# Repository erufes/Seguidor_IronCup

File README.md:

# Seguidor_IronCup
O objetivo deste projeto é construir e aprimorar um seguidor de linha capaz de ganhar a competição da IronCup 2019. Para isso, o projeto consta de estudo, prototipagem, desing e aprimoramento.  https://www.robocore.net/eventos/ironcup-2019  Edital da competição: https://www.robocore.net/upload/attachments/robocore__regras_seguidor_de_linha_108.pdf

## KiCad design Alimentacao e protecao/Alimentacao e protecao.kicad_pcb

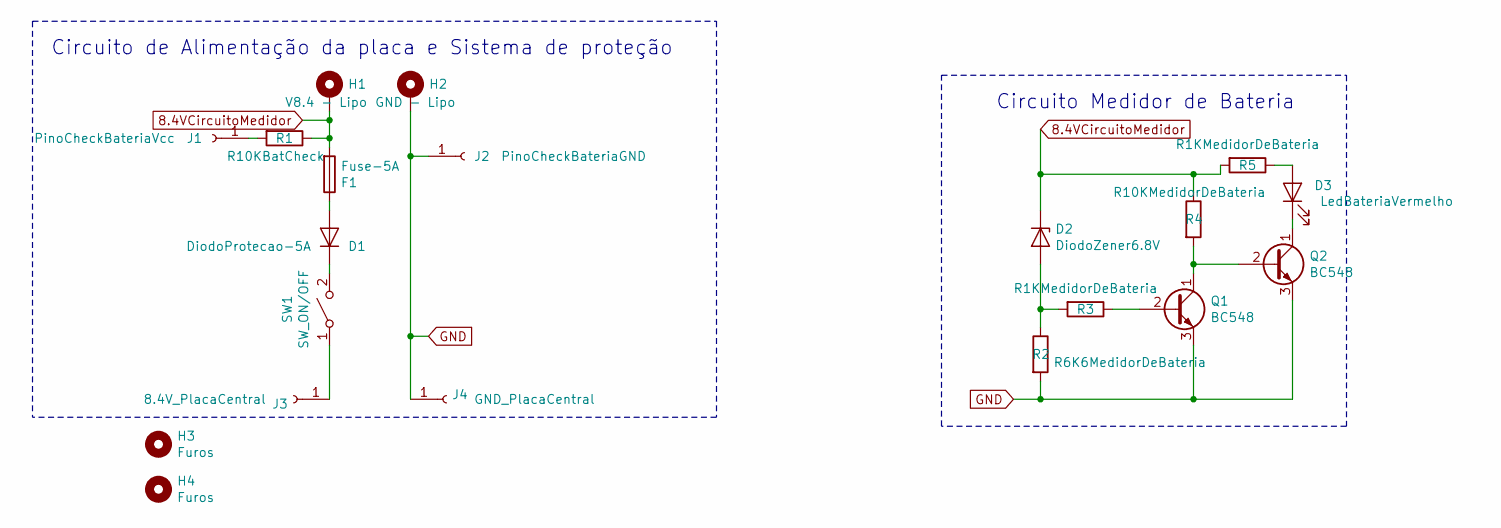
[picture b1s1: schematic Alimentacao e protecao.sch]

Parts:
D1: DiodoProtecao-5A; D_DO-27_P15.24mm_Horizontal
D2: DiodoZener6.8V; D_DO-35_SOD27_P10.16mm_Horizontal
D3: LedBateriaVermelho; LED_D3.0mm
F1: Fuse-5A; Fuseholder_Cylinder-5x20mm_Stelvio-Kontek_PTF78_Horizontal_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
H1: V8.4 - Lipo; SolderWirePad_1x01_Drill1.5mm
H2: GND - Lipo; SolderWirePad_1x01_Drill1.5mm
H3, H4: Furos; SolderWirePad_single_2-5mmDrill
J1: PinoCheckBateriaVcc; PinSocket_1x01_P2.54mm_Vertical
J2: PinoCheckBateriaGND; SolderWirePad_1x01_Drill1.5mm
J3: 8.4V_PlacaCentral; SolderWirePad_1x01_Drill1.2mm
J4: GND_PlacaCentral; SolderWirePad_1x01_Drill1.2mm
Q1, Q2: BC548; TO-92_Wide
R1: R10KBatCheck; R_Axial_DIN0207_L6.3mm_D2.5mm_P10.16mm_Horizontal
R2: R6K6MedidorDeBateria; R_Axial_DIN0207_L6.3mm_D2.5mm_P10.16mm_Horizontal
R3, R5: R1KMedidorDeBateria; R_Axial_DIN0207_L6.3mm_D2.5mm_P10.16mm_Horizontal
R4: R10KMedidorDeBateria; R_Axial_DIN0207_L6.3mm_D2.5mm_P10.16mm_Horizontal
SW1: SW_ON/OFF; Solder_Pad_Custom

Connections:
8.4VCircuitoMedidor: D2.1 (K), F1.2, H1.1, R1.1, R4.1, R5.2
GND: H2.1, J2.1, J4.1, Q1.3 (E), Q2.3 (E), R2.2
unnamed: D1.1 (K), SW1.2 (B)
unnamed: D1.2 (A), F1.1
unnamed: D2.2 (A), R2.1, R3.2
unnamed: D3.1 (K), Q2.1 (C)
unnamed: D3.2 (A), R5.1
unnamed: J1.1, R1.2
unnamed: J3.1, SW1.1 (A)
unnamed: Q1.1 (C), Q2.2 (B), R4.2
unnamed: Q1.2 (B), R3.1

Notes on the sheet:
Circuito de Alimentação da placa e Sistema de proteção
Circuito Medidor de Bateria

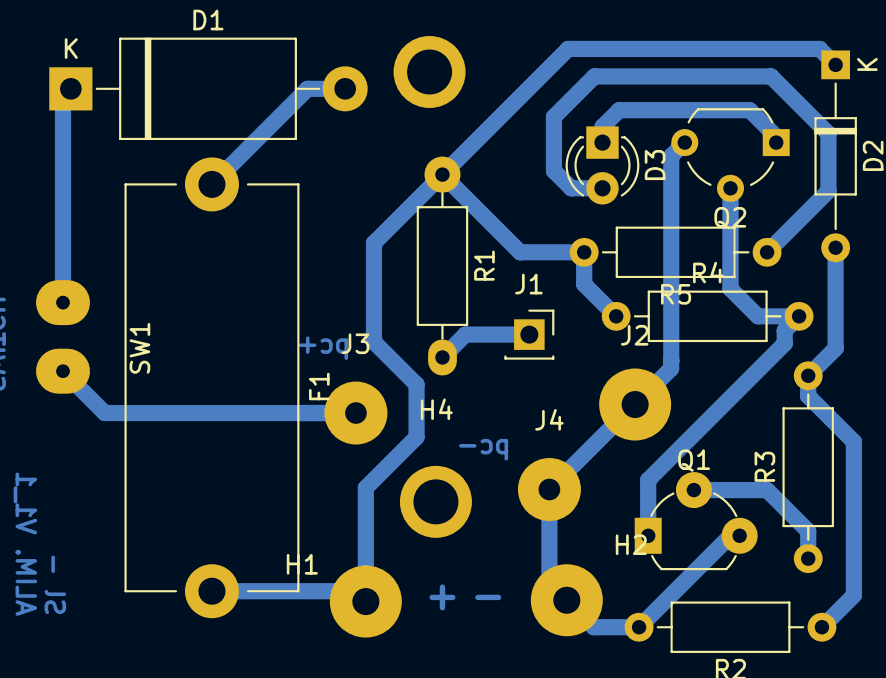
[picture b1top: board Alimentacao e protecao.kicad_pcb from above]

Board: 2 copper layers, 20 parts (0 on the bottom side), 11 nets.

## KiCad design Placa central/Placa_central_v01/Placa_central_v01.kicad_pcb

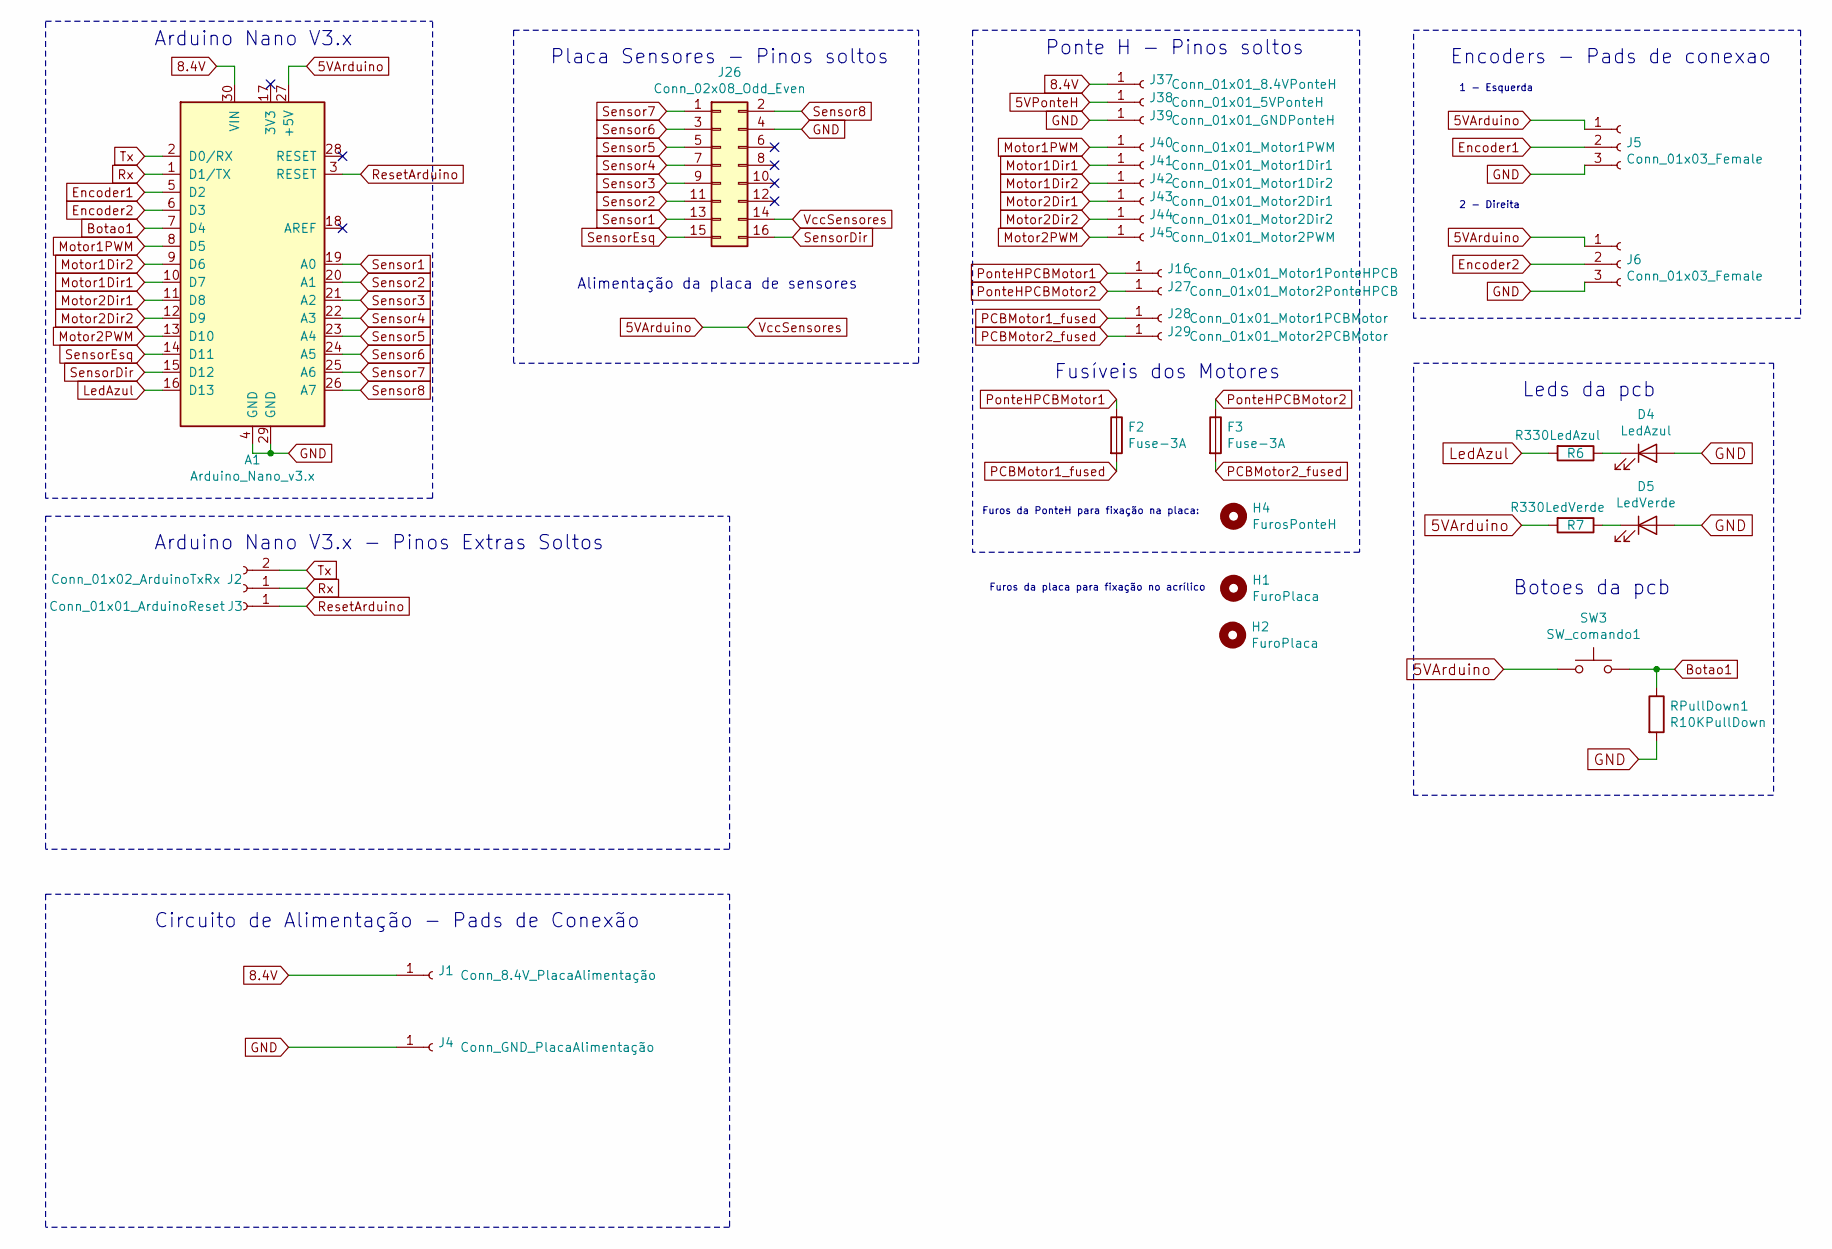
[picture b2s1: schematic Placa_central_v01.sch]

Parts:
A1: Arduino_Nano_v3.x; Arduino_Nano
D4: LedAzul; LED_D3.0mm
D5: LedVerde; LED_D3.0mm
F2, F3: Fuse-3A; Fuseholder_Cylinder-5x20mm_Stelvio-Kontek_PTF78_Horizontal_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
H1, H2: FuroPlaca; SolderWirePad_1x01_Drill2.5mm
H4: FurosPonteH; Ponte_H_furos
J1: Conn_8.4V_PlacaAlimentação; SolderWirePad_1x01_Drill1.2mm
J2: Conn_01x02_ArduinoTxRx; PinSocket_1x02_P2.54mm_Vertical
J3: Conn_01x01_ArduinoReset; PinSocket_1x01_P2.54mm_Vertical
J4: Conn_GND_PlacaAlimentação; SolderWirePad_1x01_Drill1.2mm
J5, J6: Conn_01x03_Female; Molex_KK-254_AE-6410-03A_1x03_P2.54mm_Vertical
J16: Conn_01x01_Motor1PonteHPCB; SolderWirePad_1x01_Drill1.5mm
J26: Conn_02x08_Odd_Even; IDC-Header_2x08_P2.54mm_Horizontal
J27: Conn_01x01_Motor2PonteHPCB; SolderWirePad_1x01_Drill1.5mm
J28: Conn_01x01_Motor1PCBMotor; SolderWirePad_1x01_Drill1.5mm
J29: Conn_01x01_Motor2PCBMotor; SolderWirePad_1x01_Drill1.5mm
J37: Conn_01x01_8.4VPonteH; SolderWirePad_single_1-2mmDrill
J38: Conn_01x01_5VPonteH; SolderWirePad_1x01_Drill1.2mm
J39: Conn_01x01_GNDPonteH; SolderWirePad_1x01_Drill1.2mm
J40: Conn_01x01_Motor1PWM; SolderWirePad_1x01_Drill0.8mm
J41: Conn_01x01_Motor1Dir1; SolderWirePad_1x01_Drill0.8mm
J42: Conn_01x01_Motor1Dir2; SolderWirePad_1x01_Drill0.8mm
J43: Conn_01x01_Motor2Dir1; SolderWirePad_1x01_Drill0.8mm
J44: Conn_01x01_Motor2Dir2; SolderWirePad_1x01_Drill0.8mm
J45: Conn_01x01_Motor2PWM; SolderWirePad_1x01_Drill0.8mm
R6: R330LedAzul; R_Axial_DIN0207_L6.3mm_D2.5mm_P10.16mm_Horizontal
R7: R330LedVerde; R_Axial_DIN0207_L6.3mm_D2.5mm_P10.16mm_Horizontal
RPullDown1: R10KPullDown; R_Axial_DIN0207_L6.3mm_D2.5mm_P10.16mm_Horizontal
SW3: SW_comando1; SW_PUSH_6mm_H5mm

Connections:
5VArduino: A1.27 (+5V), J5.1, J6.1, J26.14, R7.2, SW3.1
5VPonteH: J38.1
8.4V: A1.30 (VIN), J1.1, J37.1
Botao1: A1.7 (D4), RPullDown1.1, SW3.2
Encoder1: A1.5 (D2), J5.2
Encoder2: A1.6 (D3), J6.2
GND: A1.4 (GND), A1.29 (GND), D4.2 (A), D5.2 (A), J4.1, J5.3, J6.3, J26.4, J39.1, RPullDown1.2; also elsewhere on the board
LedAzul: A1.16 (D13), R6.2
Motor1Dir1: A1.10 (D7), J41.1
Motor1Dir2: A1.9 (D6), J42.1
Motor1PWM: A1.8 (D5), J40.1
Motor2Dir1: A1.11 (D8), J43.1
Motor2Dir2: A1.12 (D9), J44.1
Motor2PWM: A1.13 (D10), J45.1
unnamed: D4.1 (K), R6.1
unnamed: D5.1 (K), R7.1
PCBMotor1_fused: F2.2, J28.1
PCBMotor2_fused: F3.2, J29.1
PonteHPCBMotor1: F2.1, J16.1
PonteHPCBMotor2: F3.1, J27.1
ResetArduino: A1.3 (RESET), J3.1
Rx: A1.1 (D1/TX), J2.1
Sensor1: A1.19 (A0), J26.13
Sensor2: A1.20 (A1), J26.11
Sensor3: A1.21 (A2), J26.9
Sensor4: A1.22 (A3), J26.7
Sensor5: A1.23 (A4), J26.5
Sensor6: A1.24 (A5), J26.3
Sensor7: A1.25 (A6), J26.1
Sensor8: A1.26 (A7), J26.2
SensorDir: A1.15 (D12), J26.16
SensorEsq: A1.14 (D11), J26.15
Tx: A1.2 (D0/RX), J2.2

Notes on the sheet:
Ponte H - Pinos soltos
Arduino Nano V3.x
Leds da pcb
Botoes da pcb
Encoders - Pads de conexao
1 - Esquerda
2 - Direita
Alimentação da placa de sensores
Placa Sensores - Pinos soltos
Arduino Nano V3.x - Pinos Extras Soltos
Fusíveis dos Motores
Furos da PonteH para fixação na placa:
Circuito de Alimentação - Pads de Conexão
Furos da placa para fixação no acrílico

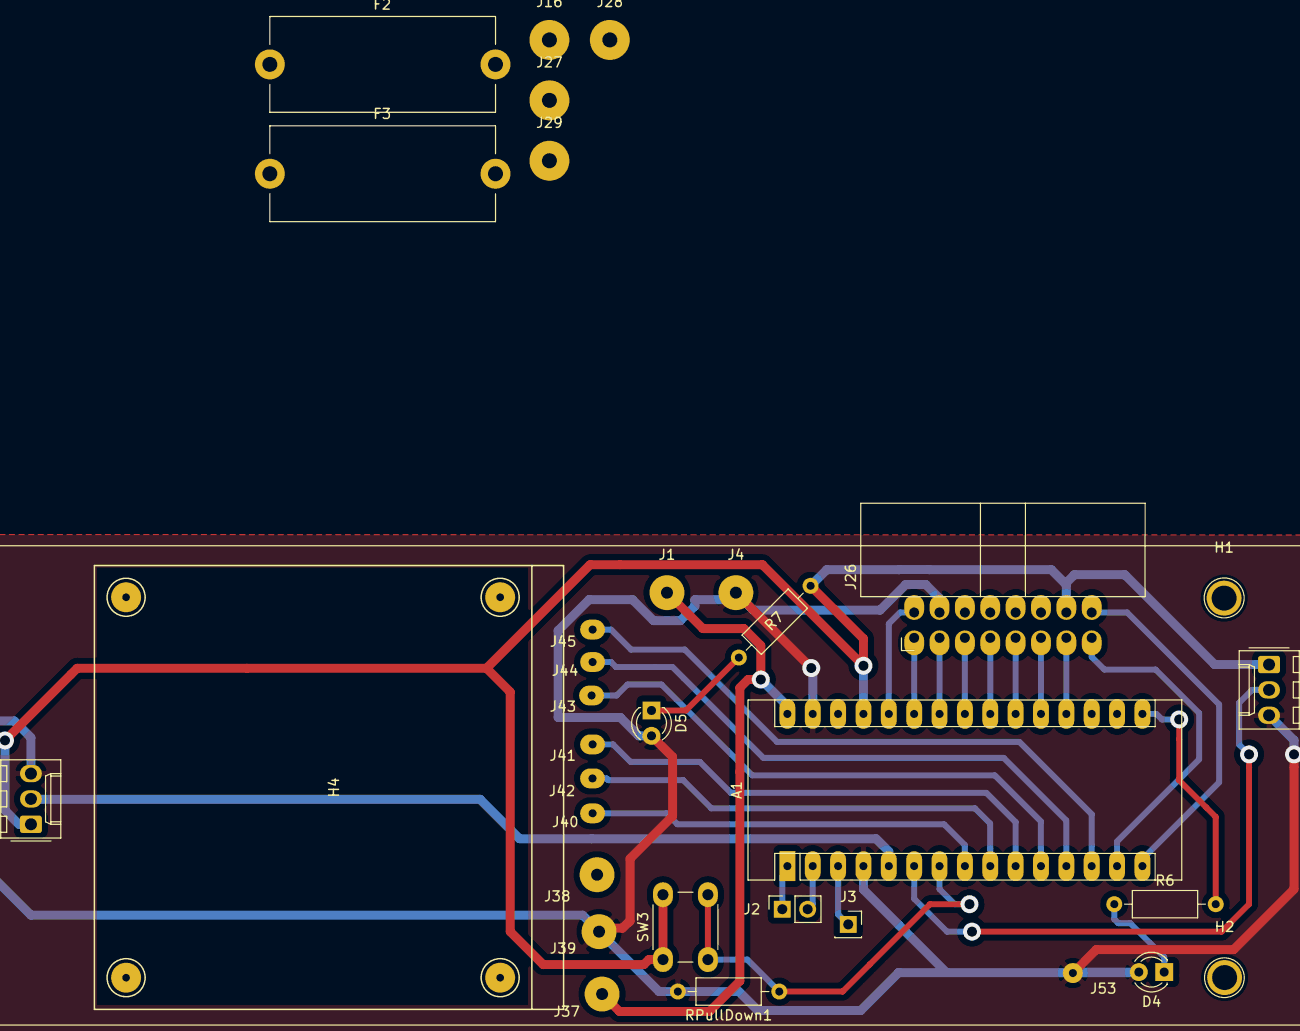
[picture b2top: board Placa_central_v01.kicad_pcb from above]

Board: 2 copper layers, 33 parts (0 on the bottom side), 32 nets.

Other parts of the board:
J53: Conn_01x01_GNDEncoderDir; SolderWirePad_1x01_Drill0.8mm

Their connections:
GND: J53.1; also elsewhere on the board

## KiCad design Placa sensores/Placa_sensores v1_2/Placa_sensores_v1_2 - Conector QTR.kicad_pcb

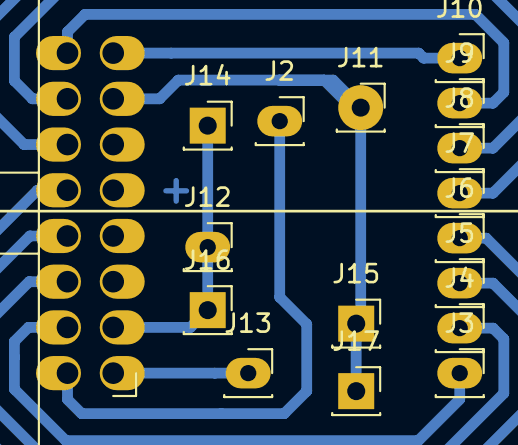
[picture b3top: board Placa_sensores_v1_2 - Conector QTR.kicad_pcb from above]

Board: 2 copper layers, 21 parts (0 on the bottom side), 12 nets.

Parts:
H1, H1#2, H1#3, H2: MountingHole; MountingHole_3mm
J1: Conn_02x08_Odd_Even; IDC-Header_2x08_P2.54mm_Horizontal
J2, J3, J4, J5, J6, J7, J8, J9, J10, J11, J12, J13, J14, J15, J16, J17: Conn_01x01_Female; PinSocket_1x01_P2.54mm_Vertical

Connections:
GND: J1.13, J11.1, J15.1, J17.1
Sensor1: J1.4, J3.1
Sensor2: J1.6, J4.1
Sensor3: J1.8, J5.1
Sensor4: J1.10, J6.1
Sensor5: J1.12, J7.1
Sensor6: J1.14, J8.1
Sensor7: J1.16, J9.1
Sensor8: J1.15, J10.1
SensorDir: J1.1, J13.1
SensorEsq: J1.2, J2.1
VccSensores: J1.3, J12.1, J14.1, J16.1

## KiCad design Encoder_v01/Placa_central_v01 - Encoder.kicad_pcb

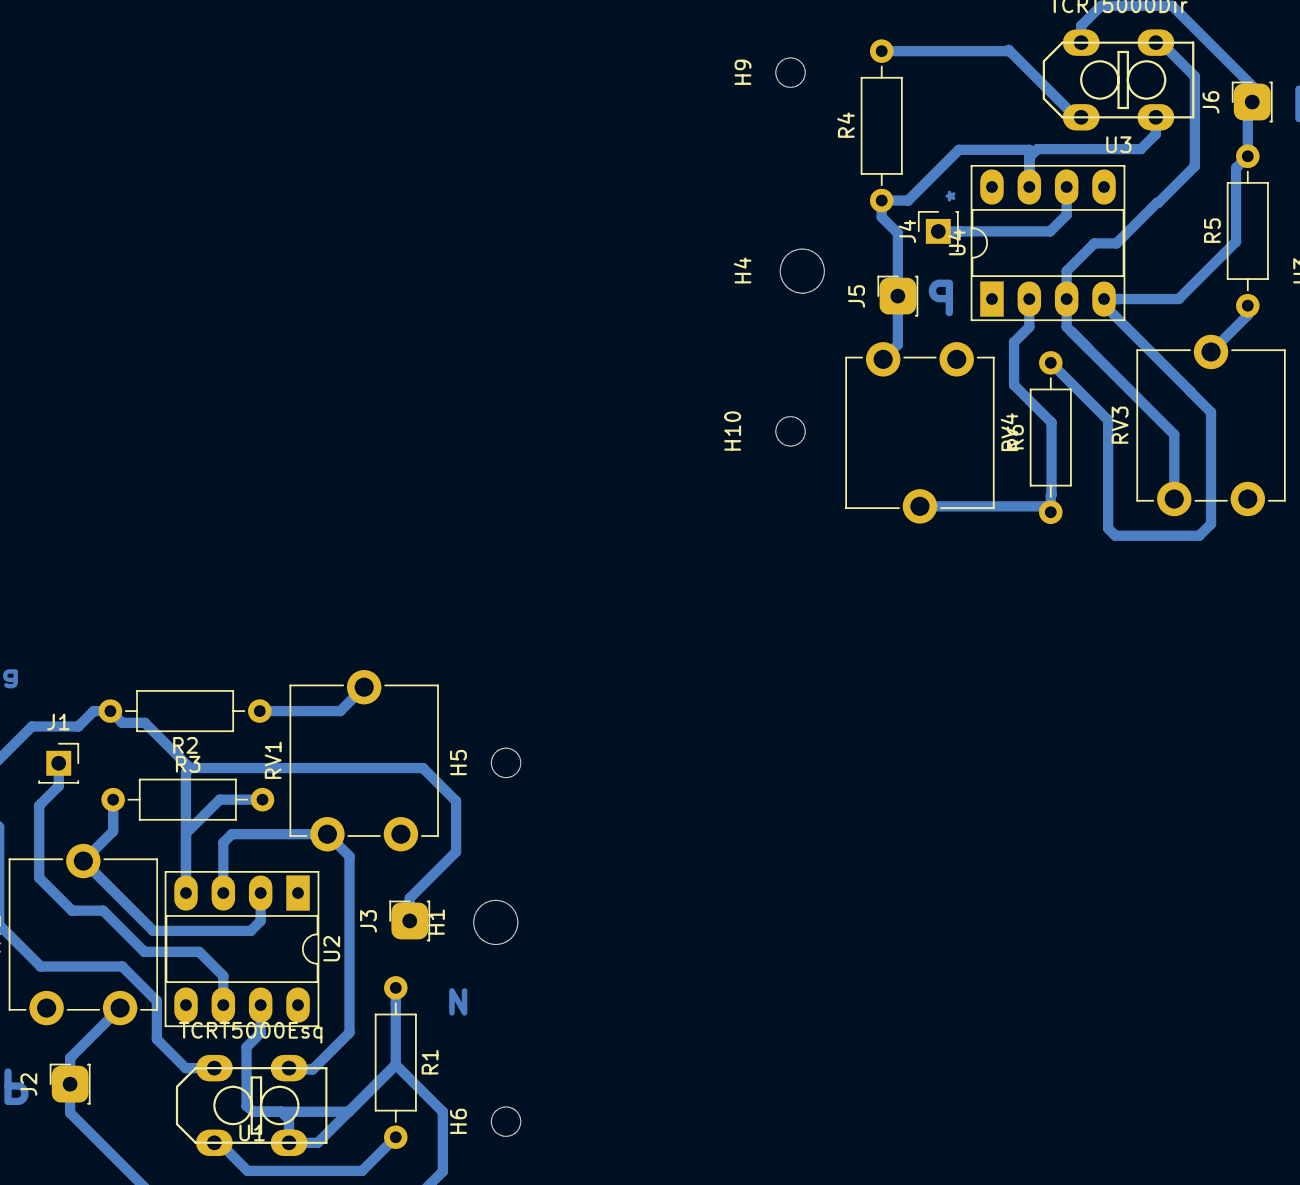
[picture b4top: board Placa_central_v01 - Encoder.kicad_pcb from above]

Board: 2 copper layers, 32 parts (0 on the bottom side), 14 nets.

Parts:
H1: Furo1Esq; MountingHole_3mm
H2: Furo2Esq; MountingHole_3mm
H3: Furo1Dir; MountingHole_3mm
H4: Furo2Dir; MountingHole_3mm
H5: Furo3Esq; MountingHole_2mm
H6: Furo4Esq; MountingHole_2mm
H7: Furo5Esq; MountingHole_2mm
H8: Furo6Esq; MountingHole_2mm
H9: Furo3Dir; MountingHole_2mm
H10: Furo4Dir; MountingHole_2mm
H11: Furo5Dir; MountingHole_2mm
H12: Furo6Dir; MountingHole_2mm
J1, J2, J3, J4, J5, J6: Conn_01x01_Female; PinSocket_1x01_P2.54mm_Vertical
R1: R220ledIREsq; R_Axial_DIN0207_L6.3mm_D2.5mm_P10.16mm_Horizontal
R2: R1KEsq; R_Axial_DIN0207_L6.3mm_D2.5mm_P10.16mm_Horizontal
R3: R10kEsq; R_Axial_DIN0207_L6.3mm_D2.5mm_P10.16mm_Horizontal
R4: R220ledIRDir; R_Axial_DIN0207_L6.3mm_D2.5mm_P10.16mm_Horizontal
R5: R1KDir; R_Axial_DIN0207_L6.3mm_D2.5mm_P10.16mm_Horizontal
R6: R10k; R_Axial_DIN0207_L6.3mm_D2.5mm_P10.16mm_Horizontal
RV1, RV2: R10KPOT_TRIMEsq; Potentiometer_ACP_CA9-V10_Vertical
RV3: R10KPOT_TRIMDir; Potentiometer_ACP_CA9-V10_Vertical
RV4: R10KPOT_TRIM; Potentiometer_ACP_CA9-V10_Vertical
U1: TCRT5000Esq; TCRT5000Extendido
U2: LM741Esq; DIP-8_W7.62mm_Socket_LongPads
U3: TCRT5000Dir; TCRT5000Extendido
U4: LM741; DIP-8_W7.62mm_Socket_LongPads

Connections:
GNDDir: J6.1, R5.2, R6.2, U3.2, U4.4
GNDEsq: J3.1, R2.2, R3.2, U1.2, U2.4
unnamed: R1.2, U1.1
unnamed: R2.1, RV1.2
unnamed: R3.1, RV2.2, U2.2
unnamed: R4.2, U3.1
unnamed: R5.1, RV3.2
unnamed: R6.1, RV4.2, U4.2
unnamed: RV1.3, U1.4, U2.3
unnamed: RV3.3, U3.4, U4.3
SinalEncoderDIr: J4.1, U4.6
SinalEncoderEsq: J1.1, U2.6
VccDir: J5.e1, R4.1, RV4.1, U3.3, U4.7
VccEsq: J2.1, R1.1, RV2.1, U1.3, U2.7

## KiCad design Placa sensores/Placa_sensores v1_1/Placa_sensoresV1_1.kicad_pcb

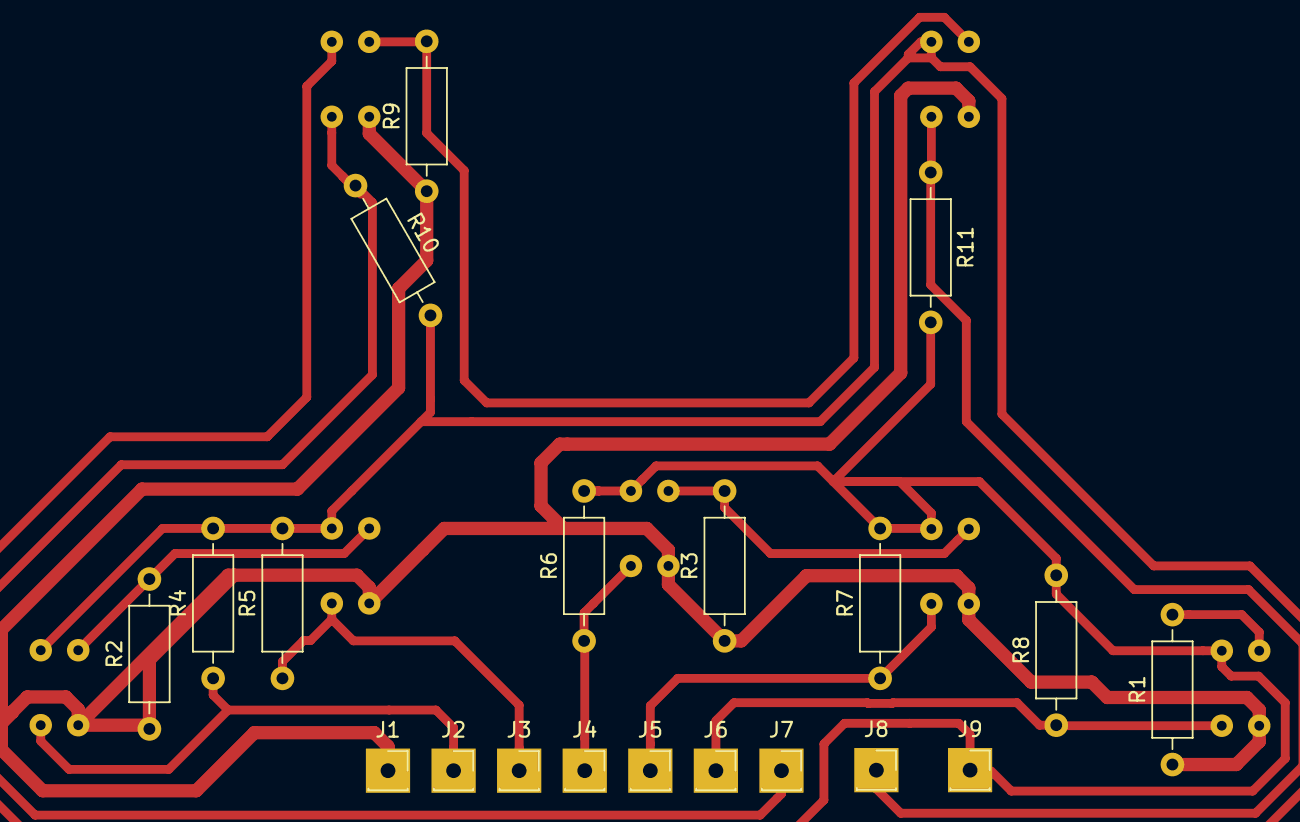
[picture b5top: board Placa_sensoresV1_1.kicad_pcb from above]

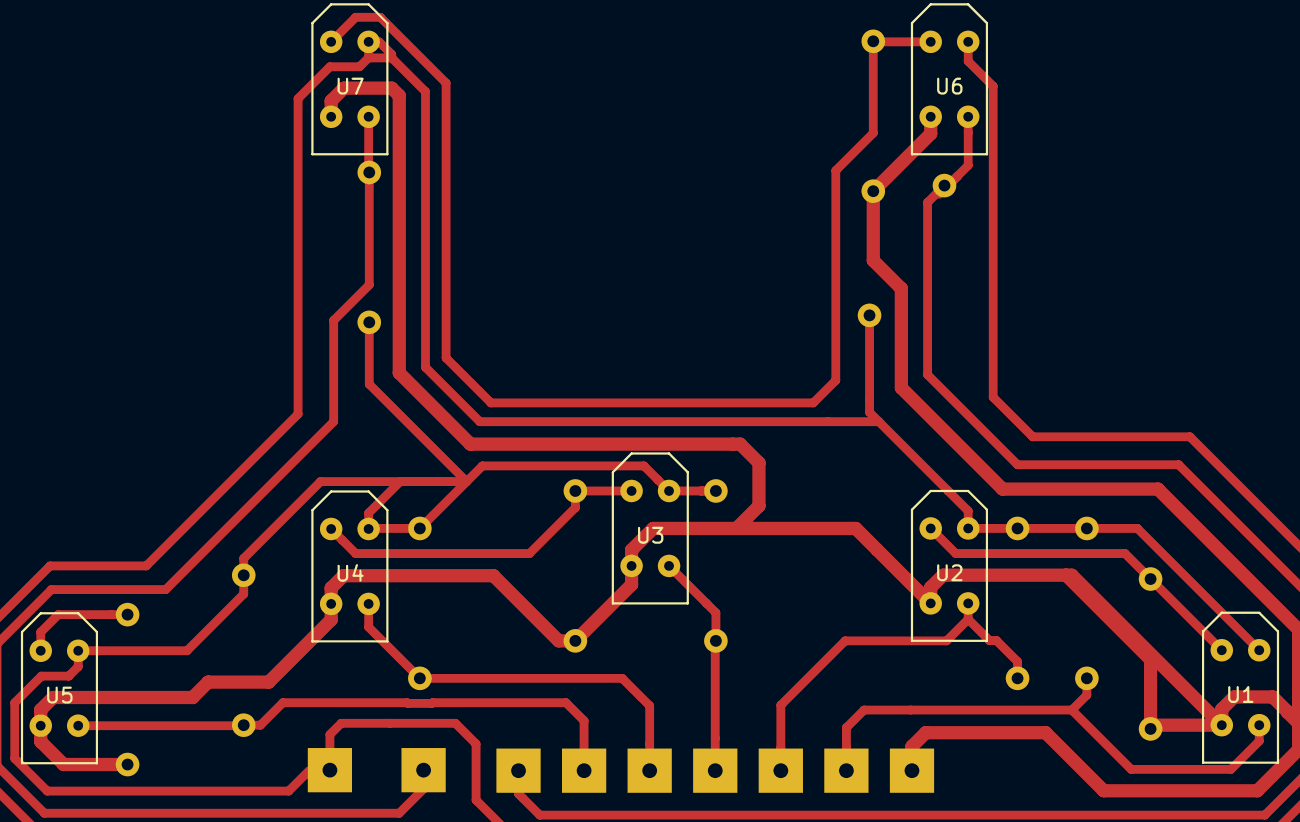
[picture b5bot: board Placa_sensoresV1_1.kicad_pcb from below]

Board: 2 copper layers, 27 parts (7 on the bottom side), 13 nets.

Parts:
J1, J2, J3, J4, J5, J6, J7, J8, J9: Conn_01x01_Female; PinSocket_1x01_P2.54mm_Vertical
R1, R2, R3, R9: 330; R_Axial_DIN0207_L6.3mm_D2.5mm_P10.16mm_Horizontal
R4, R5, R6, R7, R8, R10, R11: 10k; R_Axial_DIN0207_L6.3mm_D2.5mm_P10.16mm_Horizontal
U1, U2, U3, U4, U5, U6, U7: TCRT5000; TCRT50002

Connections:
GND: J9.1, R4.2, R5.2, R6.2, R7.2, R8.2, R10.2, R11.2, U1.2, U2.2, U3.2, U4.2, U5.2, U6.2, U7.2
unnamed: R1.2, U5.1
unnamed: R2.2, U1.1, U2.1
unnamed: R3.2, U3.1, U4.1
unnamed: R9.2, U6.1, U7.1
S1: J2.1, R4.1, U1.4
S2: J3.1, R5.1, U2.4
S3: J4.1, R6.1, U3.4
S4: J5.1, R7.1, U4.4
S5: J6.1, R8.1, U5.4
S6: J7.1, R10.1, U6.4
S7: J8.1, R11.1, U7.4
VCC: J1.1, R1.1, R2.1, R3.1, R9.1, U1.3, U2.3, U3.3, U4.3, U5.3, U6.3, U7.3

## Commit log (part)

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2019-01-30 Project initiated
2019-02-01 Construido um sistema basico de classes.
2019-02-01 asdasdasd
2019-02-01 Função WaitForRelease criada
2019-02-01 Variáveis escritas
2019-02-01 feito setspeeds e mudança no calibratelinesensors
2019-02-01 whyyy
2019-02-01 problemas
2019-02-01 Retiradas as entradas das funções preCalibration e calibrateLineSensors (variáveis globais não necessitam de serem passadas como parâmetro)
    Construída a função readLine
2019-02-01 Corrigidos os nomes de variaveis no setup e loop.
    Código inicial terminado.
2019-02-05 codigo compilavel
2019-02-28 Adicionado arquivo contendo protocoçlos de inicio e fim de corrida O codigo tomou como base a pinagem do arquivo _4motores, mas o codigo é feito para um chassi de 2 motores.
2019-03-01 example commit
2019-03-01 example cmd line commit
2019-03-01 Example corrected
2019-03-06 Create layout papel.kicad_wks
    pagina de layout de pcb em branco. Util pra imprimir na transparência
2019-03-07 V1.01
    Adicionado as variáveis das bibliotecas.
    Começo do desenvolvimento do esquemático da pcb. Feito: módulo encoder; modulo 7805;
2019-03-07 L298 pcb
    Adicionado o componente da ponte H a ser utilizada na pcb.
2019-03-08 V1.2.1 com Led on/off e Pad de gnd.
    Esquemático terminado e ja associado com os componentes.
2019-03-18 calibracao ainda nao testada
2019-03-22 Finalizado código de linha de chegada
    Primeiro teste (protoboard) concluído
2019-03-29 prototipo1 com calibracao nao tao certa
2019-04-17 ainda em desenvolvimento
2019-04-17 em desenvolvimento
2019-04-22 Criada branch separada para PBC
2019-04-22 Criada branch para a placa vermelha
2019-04-22 pasta main renomeada para arquivo
2019-04-22 commit de teste
2019-04-26 esta no branch da placa final
2019-05-17 codigo revisado
2019-06-13 teste de leitura da marcação, funcionando
2019-06-17 Rename teste_chegada.ino to leitura_chegada.ino
2019-06-20 Aprimorado trabalho ja feito
    Separando os arquivos da maneira correta, criando a biblioteca, associando componentes certos, acertando questão de variáveis de PATH e etc.
    Tentativa de criar uma metodologia para as libraries e outros documentos do projeto.
2019-06-20 Acertada mais questões de libraries
    Removi as que nao são necessárias e coloquei os componentes em novas bibliotecas, "Componentes soltos" para a pcb e "Sensores..." para o tcrt e o arduino.
2019-06-27 Organizado Pcb
    Adicionado circuito de alimentação
2019-06-30 Terminado o esquemático do circuito
    Feito: circuito medidor de bateria; pads do arduino; pads do encoder; pads da ponte H; pads da placa de sensores;
2019-06-30 Acertada nomeclatura do encoder
    De encoder1 para encoderEsq e a mesma coisa pro outro.
2019-07-02 Rename teste1_chegada to teste1_chegada.ino
2019-07-15 Acertado circuito e adicionado fusíveis
    Removido o circuito de carga da bateria; retirado os jack; adicionado os fusíveis; e antes de cada motor
2019-07-15 Acertado a placa de sensores
    Acertado biblioteca, esquemático, conexão entre as placas e só.
2019-07-17 Adicionados os componentes à PBC - ainda não posicionados corretamente
2019-07-22 codigo parcialmente comentado
    falta mais comentarios e modularização.
2019-07-22 Bordas da PCB delimitadas e pinos agrupados
2019-07-23 feita a divisão de placas, pinos extras pendentes
2019-07-27 Circuito medidor de bateria aglutinado a placa central
2019-07-27 Placa auxiliar de alimentacao rooteada, placa central AINDA DESATUALIZADA
2019-07-29 Adicionado Placa de Encoder
    Começado a placa.
    Tudo pronto para root, só falta isso
2019-07-30 terminando de implementar as fuções de marcação
2019-07-31 Tentativa de root placa de encoder
    placa da direita rooteada e a placa da esquerda em processo.
2019-07-31 Pinos extras removidos
2019-08-03 Distribuição dos compenentes praticamente concluída, quase pronta para root.
    Placa Central: 5VArduino(pino 15) colocado no pino 16, enquanto o sensorEsq(pino 16) foi colocado no pino 15 para
    facilitar o root; Adicionado na placa central os pads de conexao das alimentacoes provenientes do circuito de
    alimentacao; Label '5V' substituída por '5VArduino' - decisão a ser revisada; Pads de solda trocados por pads maiores
    por questoes de corrente alta (pinos de alimentacao). *Placa de Alimentação: Nome de dois pinos da placa de alimentação
    modificados. Pads de solda trocados por pads maiores por questoes de corrente alta (pinos de alimentacao).
2019-08-05 Separação do projeto do encoder em pasta
    Separação em uma pasta separada e preparação da placa de encoder para impressão.
2019-08-07 Feito cópia do projeto da PBC Central com novo root contendo mudanças nas Clearances e Track Widths.
    Criada nova pasta com cópia da placa central - nova tentativa de root com dimensões diferentes;
    Track Width padrão modificada para 0.6 mm;
    Clearance padrão modificada para 0.6 mm;
    Criado novo conjunto de net class 'POWER' - utilizado para trilhas de alimnentação;
    Criado novo conjunto de net class 'Critical Long trails' - utilizado para trilhas muito longas e críticas para o funcionamento do circuito.
2019-08-07 Ajustadas as dimensões e posições dos limites da PBC central e dos furos. Ajustar a posição dos limites da PBC em relação ao furo da ponte H está penente.
2019-08-07 Adicionada a zona de malha de ground, furos pendentes.
    A zona de ground ainda não foi preenchida pois os furos da placa para fixação no acrílico requerem atualização.
2019-08-15 Código da PlacaFinal adaptado para funcionar com ambas as placas, mediante mudança de apenas uma variável
2019-08-16 Preparação da placa encoder para impressão
    E mexido na placa central: adicionado gnd na placa de cima e keep out area
2019-08-16 Reajustadas as dimensçoes das placas
2019-08-16 Criado pdf para impressão
2019-08-17 Placa de alimentação finalizada e pronta para manunfatura
    Foram colocados textos indicadores próximos a pinos de destaque
    Os pinos de conexão da bateria estão indicados com + e -
    Os pinos a serem conectados na PC(Placa central) estão indicados com os símbolos pc+ e pc-
    Foi reservada uma área para ser colocado o botão, indicada por texto
    Foram adicionados também furos para parafusos
2019-08-21 exclui o arquivo de pinagem pq so tinha uma funcao
2019-08-22 Correção nas pcbs
    Nome da placa de encoder desinvertido
    Trilhas laterais de GND da placa central mais espaçadas nos cantos
    Nome da equipe colocado na placa central
2019-08-29 Adicionado adaptador para a placa QTR
2019-09-02 Removidos arquivos desatualizados da master
    A partir de agora o codigo operacional mais recente sera mantido na master
2019-09-04 Mudancas criticas na PCB Central, ainda ha pendencias
    Foi trocado o pino do botao pelo pino do encoder. Os encoders devem estar obrigatoriamente nos pinos D2 e D3:
    Encoder2 para o pino 6 (D3)
    Botao1 para o pino 7 (D4);
    Aumentadas as dimensoes dos pads conectores do arduino, para mais seguranca ao furar;
    Pads do conector modificados para melhor seguranca ao furar;
    Clearance da malha de ground aumentada de 0.5 para 0.7
2019-09-06 Alterados os pinos dos motores no codigo para corresponder `as conexoes das placas
    Motor1 = direita
    Motor2 = esquerda
    pinos do motor da esquerda se tornaram {8, 9, 5}
    pinos do motor da direita se tornaram {7, 6, 10}
2019-09-07 mudança nos pinos dos motores
2019-09-07 Modificados os códigos de testeEncoder e main
    Ambos: Tempo de amostragem da velocidade (tAlvo) modificado para 50ms (valor definitivo)
    Ambos: Diametro da roda ajustado para o valor da roda do pololu - 3.19 cm
    main: função ajustaVelocidade foi desinvertida
    testeEncoder: pinos dos motores modificados para o padrão correto
    testeEncoder2 passou a ser utilizada. Trechos de códigos desnecessários para o teste do PID do encoder foram removidos do arquivo
    testeEncoder2: Retirou-se o fator multiplicador da roda na função 'anda', ela impedia o motor direito de rodar.
2019-09-08 Modificacoes realizadas no PID do encoder
    O codigo foi comentado para um melhor entendimento do PID, com descricoes de cada uma das variaveis e o que ela representa para o sistema de controle.
    Foi adicionado um termo na constante derivativa, o tAlvo. Em meio a pesquisa, descobriu-se que e muito provavel que mudar o tAlvo alterara o comportamento do PID, conportamento que precisa ser ocmpen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
2019-09-08 PID do encoder foi modificado completamente, usando como exmplo o codigo de controle do daniel (e consequentemente a equação dele). O código do daniel está na pasta "arquivo/exemplos Daniel/aulaPID" 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
    uk = sinal de saida do controle
    uk1 = sinal de saida anterior do controle
    Kp = constante proporcional
    Kd = constante derivativa
    Ki = constante integrativa
    ek = erro atual
2019-09-08 Retirado o inicio do if experimental do PID do encoder, sera implementada no proximo teste
2019-09-09 Codigo preparado para testes de tempo - CUIDADO
    Pino do botao aparentemente nao estava configurado como entrada nem como saida. Ele foi temporariamente configurado como saida para efeito de medicao da velocidade real de atualizacao da velocidade.
    Os trechos de coigo relativos a testes deverao ser retirados uma vez finalizados os testes.
2019-09-10 Retirado um delay(80) do loop princi[pal. Nao deve ser usado delay junto com o PID
2019-09-10 testeEncoder2: Fix em função ajustaVelocidade, na feature de bloqueio de roda reversa
    Fix nos prints em serial - astensões estavam invertidas em relações às velocidades na hora de imprimir
    Pinos das velocidades estavam invertidos
    PID aivado, ainda não efetivo
2019-09-12 Pasta main desatualizada movida para arquivo
2019-09-12 adicionado funcoes de marcacao
2019-09-12 testando cruzamento
2019-09-12 marcacoes funcionando
2019-09-13 tava andando reto
2019-09-13 calibracao atualizada
2019-09-13 colocado comentario
2019-09-13 Merged develop into master manually
2019-09-13 ready to race
2019-09-13 Modificadas constantes e volcidades
2019-09-13 mudanca nas constantes
2019-09-13 codigo ainda nao funcional
2019-09-13 Codigo de linha de chegada agora esta funcional
2019-09-14 descoberto o erro de velocidade
    tava dando return no erro ao inves de limita-lo
    estava assim porque o erro era tratado no encoder, algo to tipo
2019-09-14 melhorando
2019-09-14 ajuste de constantes
2019-09-14 Revert "problemas ocorreram, nao funcional"
    This reverts commit 450d15c753a4a65463a730146b550321e57cf988.
2019-09-14 Updated with last functional code 14/09/2019 5h47
2019-09-14 ajustando pos competicao
2019-09-15 Cancela_marcacao = 0 para curvas e time filter
    Adicionado o filtro de tempo e mudado a linha 108 do código de leitura
2019-09-15 Codigo rebobinado para versao anterior
2019-09-15 Codigo que rodou na pista de fato
    chegada = 40
    curva = 40
2019-09-15 Atualizado com o ultimo codigo que rodou na tomada de tempo
2019-09-19 Atualizado para trabalhar com o motor de 1k
2019-10-23 A variavel VELCALIB agora regula a velocidade de calibração
    A variável VELCALIB não estava sendo utilizada para regular a velocidade de calibração. Quando ela é colocada como a velocidade de calibração, o robo roda loucamente.
    Isso se deve à função anda, que tem uma feature de quando a velocidade passada como parametro é menor que a VELMIN, a outra roda gira ao contrário. Foi feita uma nova função chamada andaPure, que ape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
2019-10-23 Robo pronto para apresentação na biblioteca
2020-02-04 Removido código de teste de telemetria
    Adicionada pasta para códigos de teste
2020-02-13 Removidos códigos de testes desnecessários
2020-02-13 Códigos de teste padrão serão movidaos para a master
2020-02-13 Código de teste de encoder presente na master foi favorecido
    O código de teste de encoder presente na master foi escolhido como código de teste padrão, enquanto o código de teste de encoder do branch "placa_final_develop" foi descartado
2020-02-27 Continuação dos acertos finais
    Foram acertadas as pastas e projetos da placa de sensores. Separando em dois projetos diferentes e ligando eles por um projeto hierárquico.
    Falta para ser feito a da placa central e por fim, juntar tudo em um projeto só.
